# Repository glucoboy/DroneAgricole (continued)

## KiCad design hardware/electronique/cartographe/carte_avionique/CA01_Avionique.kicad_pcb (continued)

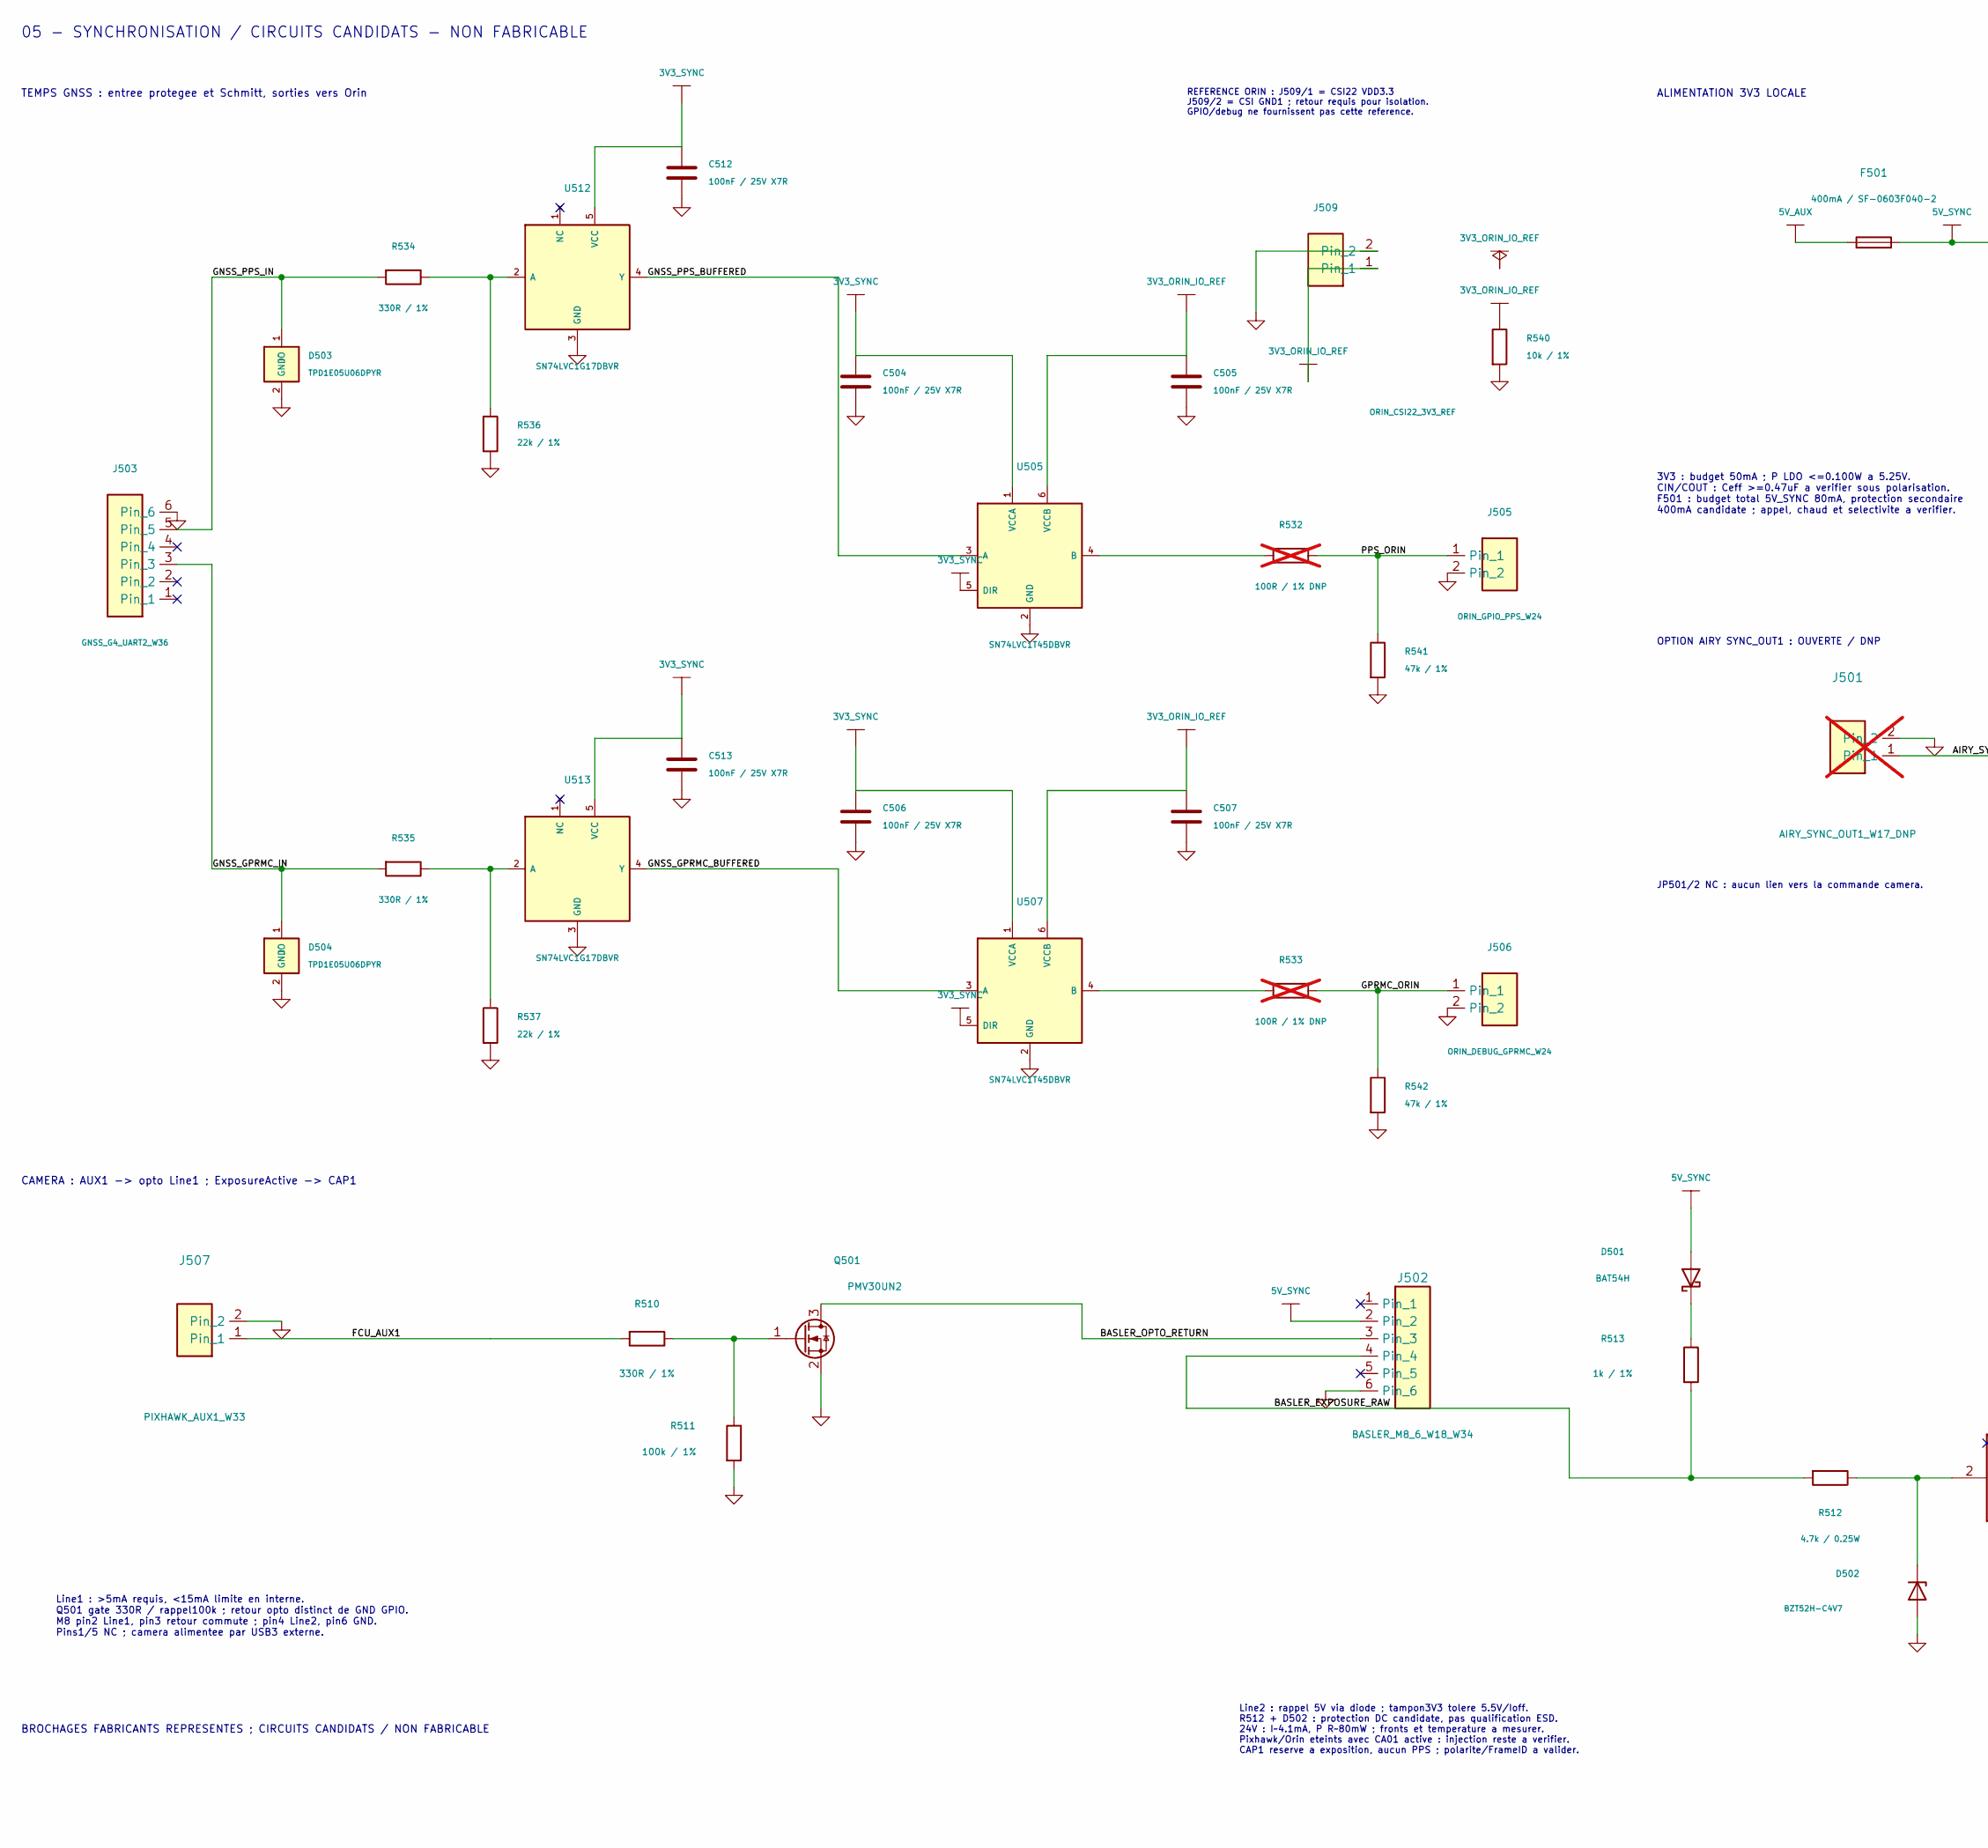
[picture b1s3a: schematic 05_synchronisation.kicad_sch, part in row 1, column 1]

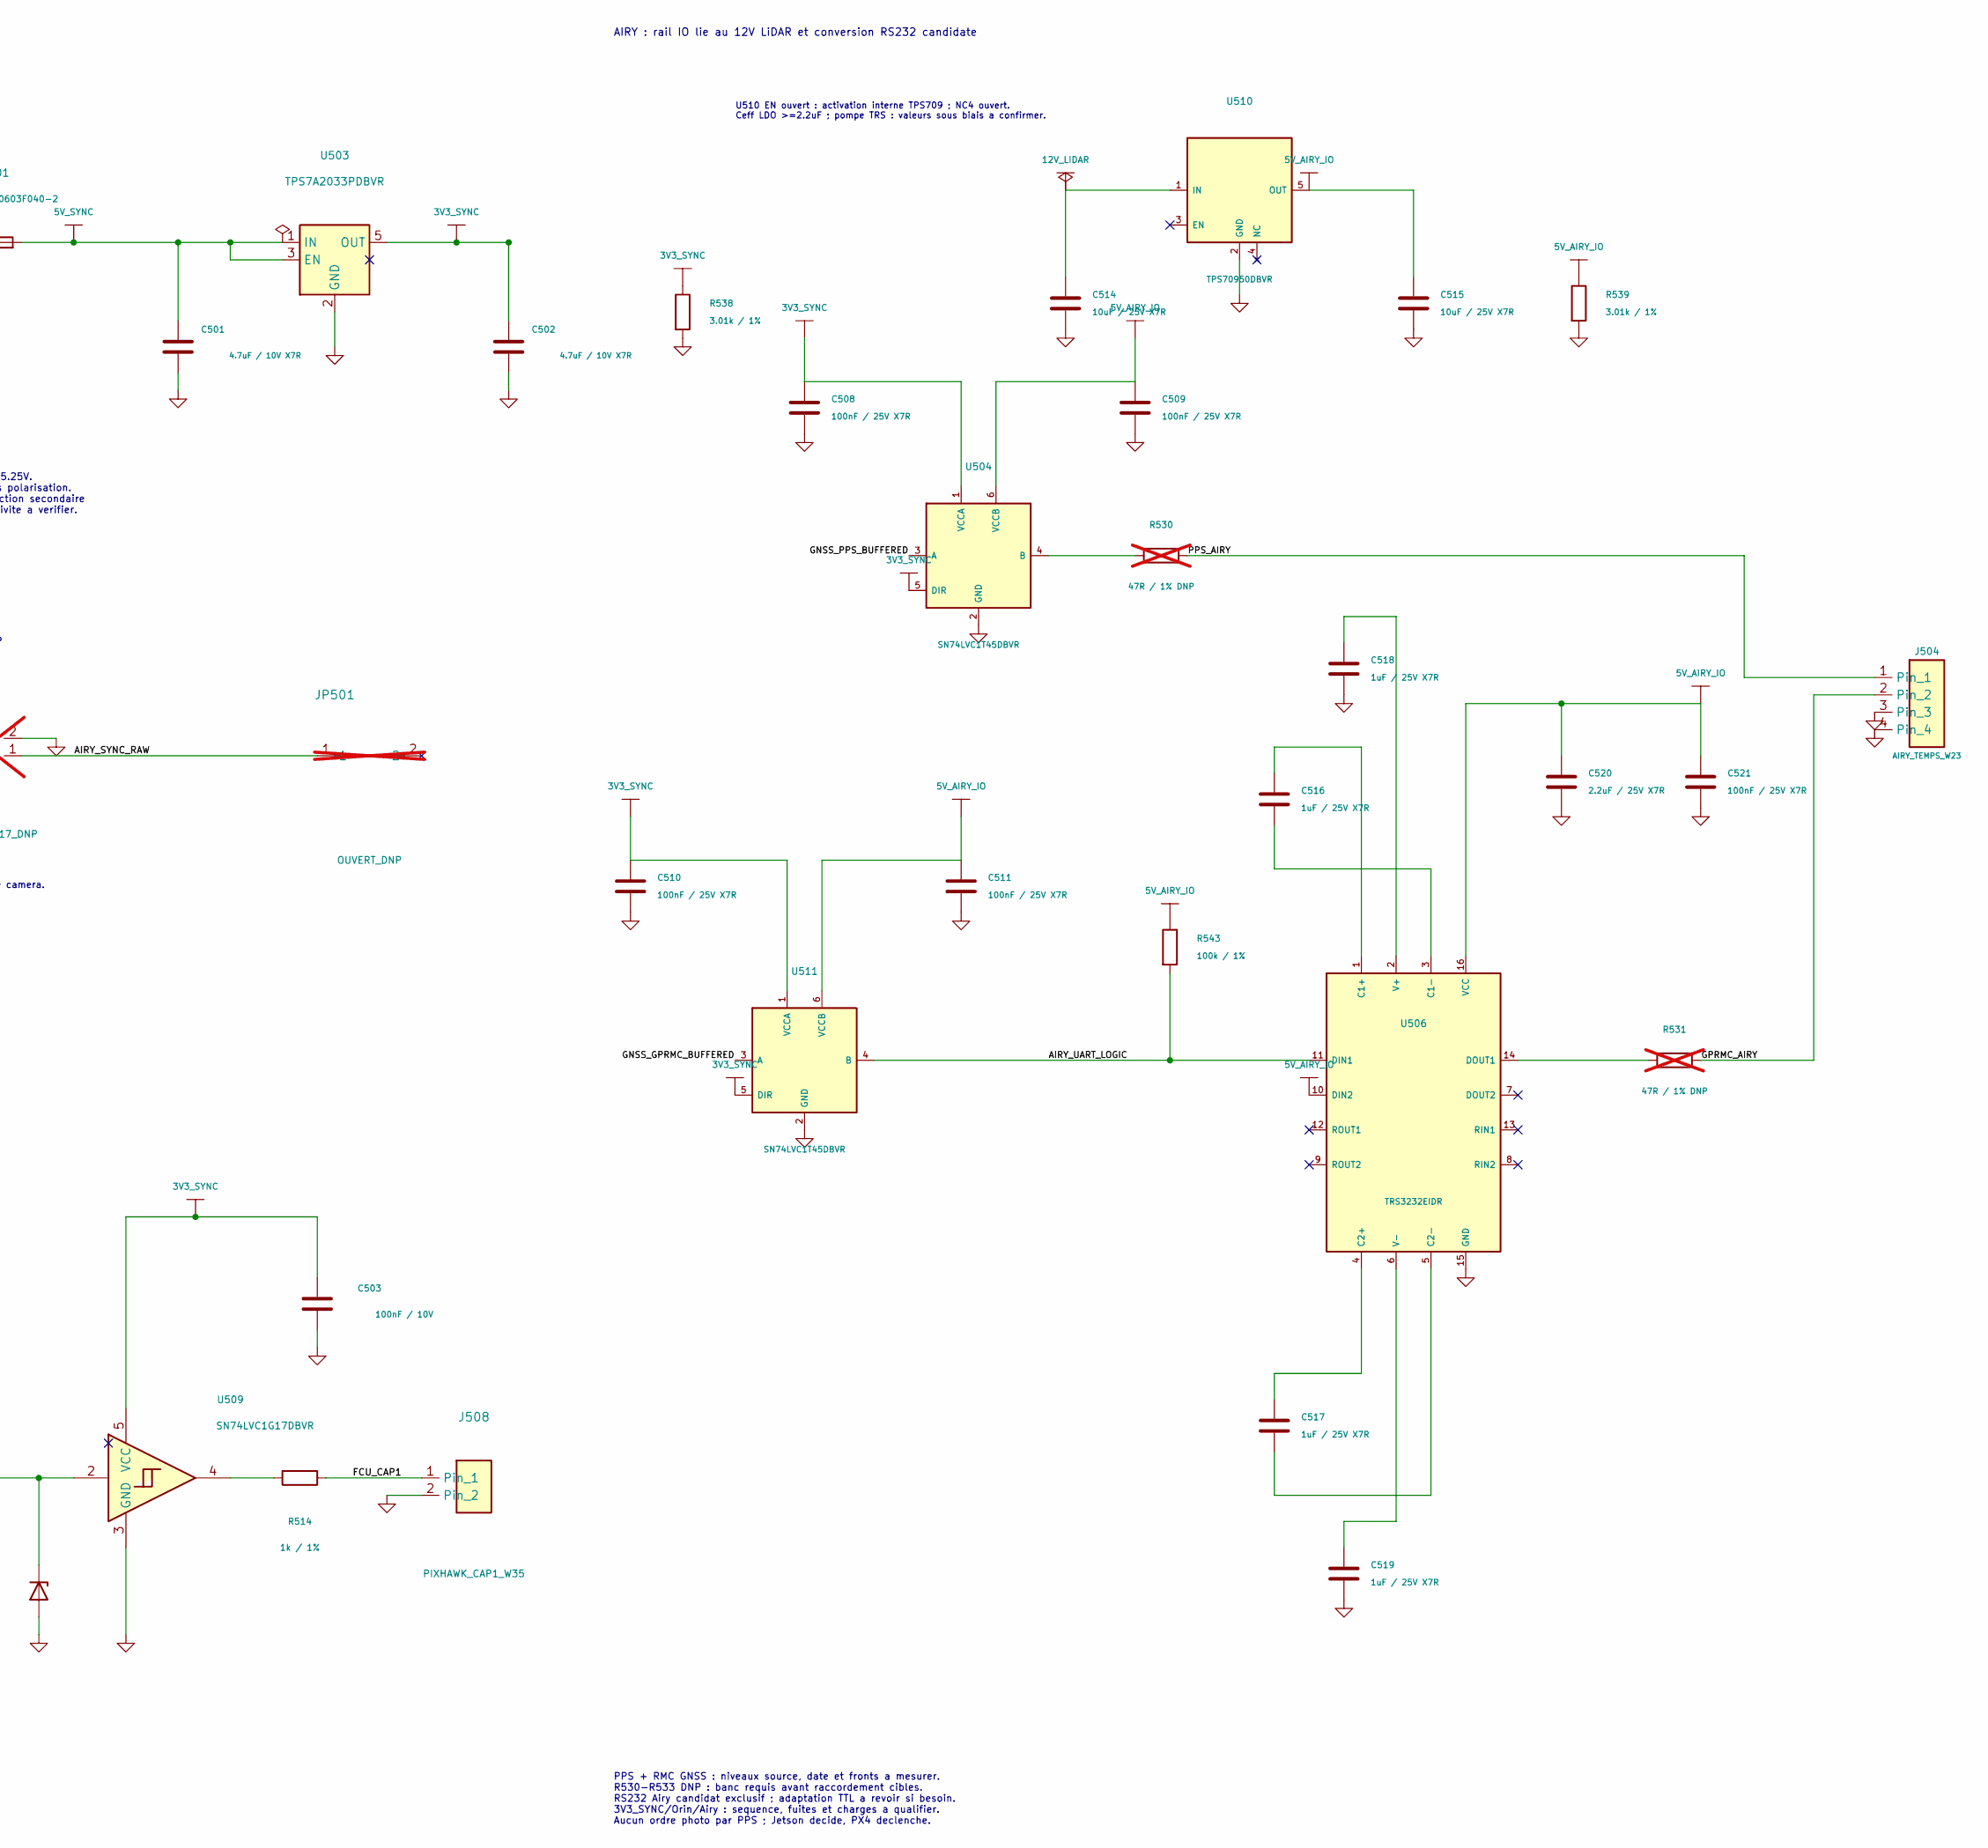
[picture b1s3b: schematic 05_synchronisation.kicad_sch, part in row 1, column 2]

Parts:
C501, C502: 4.7uF / 10V X7R; C_0805_2012Metric
C503: 100nF / 10V; C_0603_1608Metric
C504, C505, C506, C507, C508, C509, C510, C511, C512, C513, C521: 100nF / 25V X7R; C_0603_1608Metric
C514, C515: 10uF / 25V X7R; C_1206_3216Metric
C516, C517, C518, C519: 1uF / 25V X7R; C_0805_2012Metric
C520: 2.2uF / 25V X7R; C_0805_2012Metric
D501: BAT54H; D_SOD-123F
D502: BZT52H-C4V7; D_SOD-123F
D503, D504: TPD1E05U06DPYR; Texas_DPY0002A_0.6x1mm_P0.65mm; MPN TPD1E05U06DPYR
F501: 400mA / SF-0603F040-2; Fuse_0603_1608Metric
J501: AIRY_SYNC_OUT1_W17_DNP; JST_GH_SM02B-GHS-TB_1x02-1MP_P1.25mm_Horizontal; MPN SM02B-GHS-TB(LF)(SN); not fitted
J502: BASLER_M8_6_W18_W34; JST_PH_S6B-PH-SM4-TB_1x06-1MP_P2.00mm_Horizontal; MPN S6B-PH-SM4-TB(LF)(SN)
J503: GNSS_G4_UART2_W36; JST_GH_SM06B-GHS-TB_1x06-1MP_P1.25mm_Horizontal; MPN SM06B-GHS-TB(LF)(SN)
J504: AIRY_TEMPS_W23; JST_GH_SM04B-GHS-TB_1x04-1MP_P1.25mm_Horizontal; MPN SM04B-GHS-TB(LF)(SN)
J505: ORIN_GPIO_PPS_W24; JST_GH_SM02B-GHS-TB_1x02-1MP_P1.25mm_Horizontal; MPN SM02B-GHS-TB(LF)(SN)
J506: ORIN_DEBUG_GPRMC_W24; JST_GH_SM02B-GHS-TB_1x02-1MP_P1.25mm_Horizontal; MPN SM02B-GHS-TB(LF)(SN)
J507: PIXHAWK_AUX1_W33; JST_GH_SM02B-GHS-TB_1x02-1MP_P1.25mm_Horizontal; MPN SM02B-GHS-TB(LF)(SN)
J508: PIXHAWK_CAP1_W35; JST_GH_SM02B-GHS-TB_1x02-1MP_P1.25mm_Horizontal; MPN SM02B-GHS-TB(LF)(SN)
J509: ORIN_CSI22_3V3_REF; JST_GH_SM02B-GHS-TB_1x02-1MP_P1.25mm_Horizontal; MPN SM02B-GHS-TB(LF)(SN)
JP501: OUVERT_DNP; SolderJumper-2_P1.3mm_Open_Pad1.0x1.5mm; not fitted
Q501: PMV30UN2; SOT-23
R510, R534, R535: 330R / 1%; R_0603_1608Metric
R511, R543: 100k / 1%; R_0603_1608Metric
R512: 4.7k / 0.25W; R_1206_3216Metric
R513, R514: 1k / 1%; R_0603_1608Metric
R530, R531: 47R / 1% DNP; R_0603_1608Metric; not fitted
R532, R533: 100R / 1% DNP; R_0603_1608Metric; not fitted
R536, R537: 22k / 1%; R_0603_1608Metric
R538, R539: 3.01k / 1%; R_0603_1608Metric
R540: 10k / 1%; R_0603_1608Metric
R541, R542: 47k / 1%; R_0603_1608Metric
U503: TPS7A2033PDBVR; SOT-23-5
U504, U505, U507, U511: SN74LVC1T45DBVR; SOT-23-6; MPN SN74LVC1T45DBVR
U506: TRS3232EIDR; SOIC-16_3.9x9.9mm_P1.27mm; MPN TRS3232EIDR
U509: SN74LVC1G17DBVR; SOT-23-5
U510: TPS70950DBVR; SOT-23-5; MPN TPS70950DBVR
U512, U513: SN74LVC1G17DBVR; SOT-23-5; MPN SN74LVC1G17DBVR

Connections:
3V3_ORIN_IO_REF: C505.1, C507.1, J509.1, R540.1, U505.6 (VCCB), U507.6 (VCCB)
3V3_SYNC: C502.1, C503.1, C504.1, C506.1, C508.1, C510.1, C512.1, C513.1, R538.1, U503.5 (OUT), U504.1 (VCCA), U504.5 (DIR), U505.1 (VCCA), U505.5 (DIR), U507.1 (VCCA), U507.5 (DIR), U509.5 (VCC), U511.1 (VCCA), U511.5 (DIR), U512.5 (VCC), U513.5 (VCC)
5V_AIRY_IO: C509.1, C511.1, C515.1, C520.1, C521.1, R539.1, R543.1, U504.6 (VCCB), U506.10 (DIN2), U506.16 (VCC), U510.5 (OUT), U511.6 (VCCB)
5V_AUX: F501.1; also elsewhere on the board
5V_SYNC: C501.1, D501.2 (A), F501.2, J502.2, U503.1 (IN), U503.3 (EN)
12V_LIDAR: C514.1, U510.1 (IN); also elsewhere on the board
/05_synchronisation/AIRY_SYNC_RAW: J501.1, JP501.1
/05_synchronisation/AIRY_UART_LOGIC: R543.2, U506.11 (DIN1), U511.4 (B)
/05_synchronisation/BASLER_EXPOSURE_RAW: J502.4, R512.2, R513.2
/05_synchronisation/BASLER_OPTO_RETURN: J502.3, Q501.3 (D)
/05_synchronisation/FCU_AUX1: J507.1, R510.2
/05_synchronisation/FCU_CAP1: J508.1, R514.1
/05_synchronisation/GNSS_GPRMC_BUFFERED: U507.3 (A), U511.3 (A), U513.4 (Y)
/05_synchronisation/GNSS_GPRMC_IN: D504.1 (IO), J503.3, R535.2
/05_synchronisation/GNSS_PPS_BUFFERED: U504.3 (A), U505.3 (A), U512.4 (Y)
/05_synchronisation/GNSS_PPS_IN: D503.1 (IO), J503.5, R534.2
/05_synchronisation/GPRMC_AIRY: J504.2, R531.1
/05_synchronisation/GPRMC_ORIN: J506.1, R533.1, R542.1
/05_synchronisation/PPS_AIRY: J504.1, R530.1
/05_synchronisation/PPS_ORIN: J505.1, R532.1, R541.1
GND: C501.2, C502.2, C503.2, C504.2, C505.2, C506.2, C507.2, C508.2, C509.2, C510.2, C511.2, C512.2, C513.2, C514.2, C515.2, C518.2, C519.2, C520.2, C521.2, D502.2 (A), D503.2 (GND), D504.2 (GND), J501.2, J502.6, J503.6, J504.3, J504.4, J505.2, J506.2, J507.2, J508.2, J509.2, Q501.2 (S), R511.2, R536.2, R537.2, R538.2, R539.2, R540.2, R541.2, R542.2, U503.2 (GND), U504.2 (GND), U505.2 (GND), U506.15 (GND), U507.2 (GND), U509.3 (GND), U510.2 (GND), U511.2 (GND), U512.3 (GND), U513.3 (GND); also elsewhere on the board
unnamed: D501.1 (K), R513.1
unnamed: D502.1 (K), R512.1, U509.2
unnamed: Q501.1 (G), R510.1, R511.1
unnamed: R514.2, U509.4
unnamed: R530.2, U504.4 (B)
unnamed: R532.2, U505.4 (B)
unnamed: C516.1, U506.1 (C1+)
unnamed: C516.2, U506.3 (C1-)
unnamed: C517.1, U506.4 (C2+)
unnamed: C517.2, U506.5 (C2-)
unnamed: R531.2, U506.14 (DOUT1)
unnamed: C518.1, U506.2 (V+)
unnamed: C519.1, U506.6 (V-)
unnamed: R533.2, U507.4 (B)
unnamed: R534.1, R536.1, U512.2 (A)
unnamed: R535.1, R537.1, U513.2 (A)

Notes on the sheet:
ALIMENTATION 3V3 LOCALE
3V3 : budget 50mA ; P LDO <=0.100W a 5.25V. CIN/COUT : Ceff >=0.47uF a verifier sous polarisation. F501 : budget total 5V_SYNC 80mA, protection secondaire 400mA candidate ; appel, chaud et selectivite a verifier.
OPTION AIRY SYNC_OUT1 : OUVERTE / DNP
JP501/2 NC : aucun lien vers la commande camera.
CAMERA : AUX1 -> opto Line1 ; ExposureActive -> CAP1
Line1 : >5mA requis, <15mA limite en interne. Q501 gate 330R / rappel100k ; retour opto distinct de GND GPIO. M8 pin2 Line1, pin3 retour commute ; pin4 Line2, pin6 GND. Pins1/5 NC ; camera alimentee par USB3 externe.
Line2 : rappel 5V via diode ; tampon3V3 tolere 5.5V/Ioff. R512 + D502 : protection DC candidate, pas qualification ESD. 24V : I~4.1mA, P R~80mW ; fronts et temperature a mesurer. Pixhawk/Orin eteints avec CA01 active : injection reste a verifier. CAP1 reserve a exposition, aucun PPS ; polarite/Fram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
TEMPS GNSS : entree protegee et Schmitt, sorties vers Orin
REFERENCE ORIN : J509/1 = CSI22 VDD3.3 J509/2 = CSI GND1 ; retour requis pour isolation. GPIO/debug ne fournissent pas cette reference.
AIRY : rail IO lie au 12V LiDAR et conversion RS232 candidate
U510 EN ouvert : activation interne TPS709 ; NC4 ouvert. Ceff LDO >=2.2uF ; pompe TRS : valeurs sous biais a confirmer.
PPS + RMC GNSS : niveaux source, date et fronts a mesurer. R530-R533 DNP : banc requis avant raccordement cibles. RS232 Airy candidat exclusif ; adaptation TTL a revoir si besoin. 3V3_SYNC/Orin/Airy : sequence, fuites et charges a qualifier. Aucun ordre photo par PPS ; Jetson decide, PX4 declenche.
BROCHAGES FABRICANTS REPRESENTES ; CIRCUITS CANDIDATS / NON FABRICABLE
05 - SYNCHRONISATION / CIRCUITS CANDIDATS - NON FABRICABLE

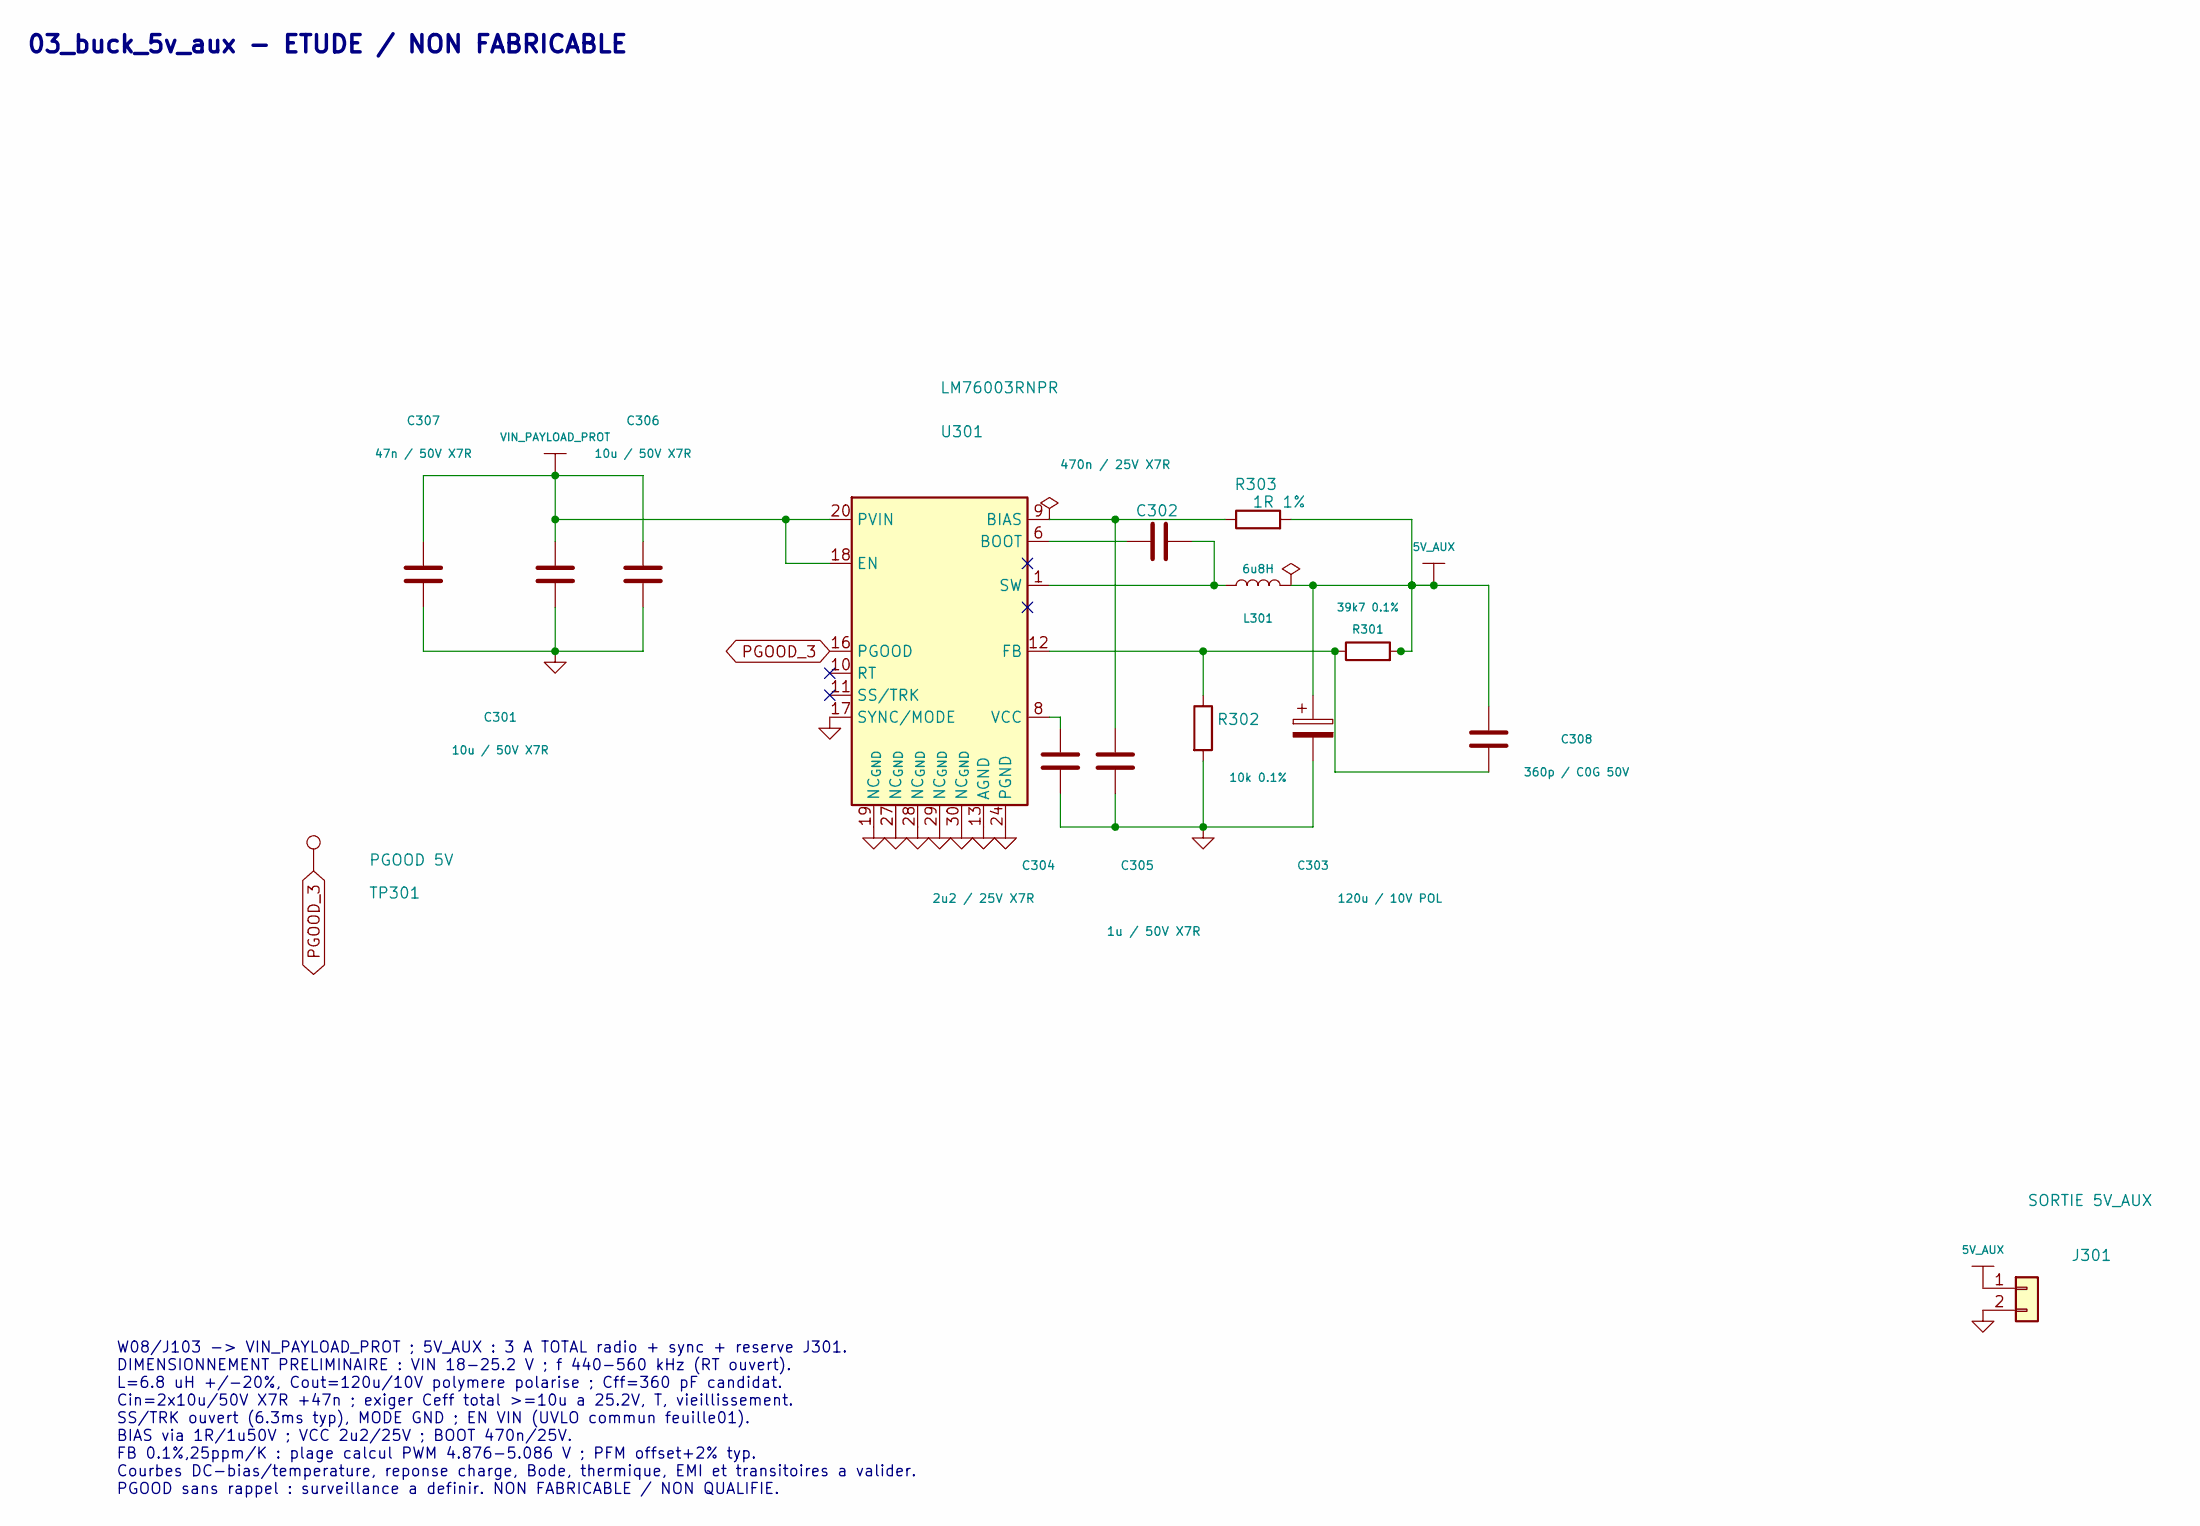
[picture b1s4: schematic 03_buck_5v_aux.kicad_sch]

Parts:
C301, C306: 10u / 50V X7R; C_1210_3225Metric; MPN C3225X7R1H106K250AC
C302: 470n / 25V X7R; C_0603_1608Metric; MPN C1608X7R1E474K080AB
C303: 120u / 10V POL; CP_Elec_6.3x5.9; MPN 10SVPC120MV
C304: 2u2 / 25V X7R; C_0805_2012Metric; MPN C2012X7R1E225K125AB
C305: 1u / 50V X7R; C_0603_1608Metric; MPN C1608X7R1H105K080AB
C307: 47n / 50V X7R; C_0603_1608Metric; MPN C1608X7R1H473K080AA
C308: 360p / C0G 50V; C_0603_1608Metric; MPN C1608C0G1H361J080AA
J301: SORTIE 5V_AUX; JST_VH_B2PS-VH_1x02_P3.96mm_Horizontal; MPN B2PS-VH(LF)(SN)
L301: 6u8H; L_Coilcraft_XAL1010-XXX; MPN XAL1010-682MED
R301: 39k7 0.1%; R_0603_1608Metric; MPN TNPW060339K7BEEA
R302: 10k 0.1%; R_0603_1608Metric; MPN TNPW060310K0BEEA
R303: 1R 1%; R_0603_1608Metric; MPN CRCW06031R00FKEA
TP301: PGOOD 5V; TestPoint_Pad_D1.5mm
U301: LM76003RNPR; TI_LM76003_RNP_ThermalVias_D0p3; MPN LM76003RNPR

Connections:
5V_AUX: C303.1, C308.1, J301.1, L301.2, R301.2, R303.2; also elsewhere on the board
GND: C301.2, C303.2, C304.2, C305.2, C306.2, C307.2, J301.2, R302.2, U301.13 (AGND), U301.14 (AGND), U301.15 (AGND), U301.17 (SYNC/MODE), U301.19 (NC_{GND}), U301.24 (PGND), U301.25 (PGND), U301.26 (PGND), U301.27 (NC_{GND}), U301.28 (NC_{GND}), U301.29 (NC_{GND}), U301.30 (NC_{GND}), U301.31 (AGND); also elsewhere on the board
unnamed: C302.2, L301.1, U301.1 (SW), U301.2 (SW), U301.3 (SW), U301.4 (SW), U301.5 (SW)
unnamed: C305.1, R303.1, U301.9 (BIAS)
unnamed: C302.1, U301.6 (BOOT)
unnamed: C308.2, R301.1, R302.1, U301.12 (FB)
unnamed: C304.1, U301.8 (VCC)
PGOOD_3: TP301.1, U301.16 (PGOOD)
VIN_PAYLOAD_PROT: C301.1, C306.1, C307.1, U301.18 (EN), U301.20 (PVIN), U301.21 (PVIN), U301.22 (PVIN); also elsewhere on the board

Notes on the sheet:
W08/J103 -> VIN_PAYLOAD_PROT ; 5V_AUX : 3 A TOTAL radio + sync + reserve J301. DIMENSIONNEMENT PRELIMINAIRE : VIN 18-25.2 V ; f 440-560 kHz (RT ouvert). L=6.8 uH +/-20%, Cout=120u/10V polymere polarise ; Cff=360 pF candidat. Cin=2x10u/50V X7R +47n ; exiger Ceff total >=10u a 25.2V, T, vieillissemen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
03_buck_5v_aux - ETUDE / NON FABRICABLE
